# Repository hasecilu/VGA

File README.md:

# VGA adapter
This is a simple PCB board for interfacing a FPGA with SIL header to a VGA connector to add video functionalities to your projects.
Designed with [KiCad](https://kicad.org/download/)

[Download here](https://gitlab.com/hasecilu/VGA/-/archive/master/VGA-master.zip)

## Important!

For updates go to the [GitLab repo](https://gitlab.com/hasecilu/VGA)

## Pictures

First render

Second render

Third render

Fourth render

Please note that the VGA board showed in the next pictures are from an older version and that's the reason there is a cable for connecting ground.
The new version has ground pins on both sides to avoid use cables (generally ground pins are at the begin/end of one SIL header in the development boards).

Perspective view

Top view

## Using the PCB

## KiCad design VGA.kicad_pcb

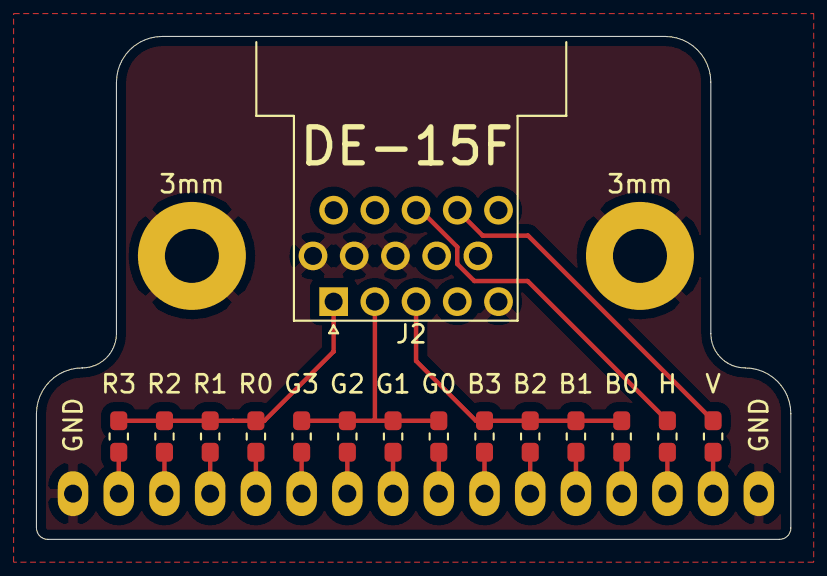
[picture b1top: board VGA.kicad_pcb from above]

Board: 2 copper layers, 41.9 x 27.9 mm, 18 parts (1 on the bottom side), 20 nets.

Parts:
3mm, 3mm#2: MountingHole_3mm_Pad
J1: Conn_01x16; PinHeader_1x16_P2.54mm_Vertical
J2: DB15_Female_HighDensity; DSUB-15-HD_Female_Horizontal_P2.29x2.54mm_EdgePinOffset9.40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
R1, R5, R9: 510; R_0603_1608Metric_Pad1.05x0.95mm_HandSolder
R2, R6, R10: 1k; R_0603_1608Metric_Pad1.05x0.95mm_HandSolder
R3, R7, R11: 2k; R_0603_1608Metric_Pad1.05x0.95mm_HandSolder
R4, R8, R12: 4k; R_0603_1608Metric_Pad1.05x0.95mm_HandSolder
R13, R14: 82; R_0603_1608Metric_Pad1.05x0.95mm_HandSolder

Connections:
/B: J2.3, R9.1, R10.1, R11.1, R12.1
/G: J2.2, R5.1, R6.1, R7.1, R8.1
/H: J2.13, R13.1
/R: J2.1, R1.1, R2.1, R3.1, R4.1
/V: J2.14, R14.1
GND: 3mm.1, 3mm#2.1, J1.1, J1.16, J2.5, J2.6, J2.7, J2.8, J2.10
unnamed: J1.2, R14.2
unnamed: J1.3, R13.2
unnamed: J1.4, R12.2
unnamed: J1.5, R11.2
unnamed: J1.6, R10.2
unnamed: J1.7, R9.2
unnamed: J1.8, R8.2
unnamed: J1.9, R7.2
unnamed: J1.10, R6.2
unnamed: J1.11, R5.2
unnamed: J1.12, R4.2
unnamed: J1.13, R3.2
unnamed: J1.14, R2.2
unnamed: J1.15, R1.2

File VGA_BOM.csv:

"Source:","/home/uli/Documents/KiCAD/Boards/VGA/VGA.sch"
"Date:","Fri 13 Dec 2019 15:05:54 CST"
"Tool:","Eeschema 5.1.5-52549c5~84~ubuntu18.04.1"
"Generator:","/usr/share/kicad/plugins/bom_csv_grouped_by_value.py"
"Component Count:","16"

"Individual Components:"

"Item","Qty","Reference(s)","Value","LibPart","Footprint","Datasheet"
"","","J1","Conn_01x16","Connector_Generic:Conn_01x16","Connector_PinHeader_2.54mm:PinHeader_1x16_P2.54mm_Vertical","~"
"","","J2","DB15_Female_HighDensity","Connector:DB15_Female_HighDensity","Connector_Dsub:DSUB-15-HD_Female_Horizontal_P2.29x2.54mm_EdgePinOffset9.40mm"," ~"
"","","R1","510","Device:R","Resistor_SMD:R_0603_1608Metric_Pad1.05x0.95mm_HandSolder","~"
"","","R2","1k","Device:R","Resistor_SMD:R_0603_1608Metric_Pad1.05x0.95mm_HandSolder","~"
"","","R3","2k","Device:R","Resistor_SMD:R_0603_1608Metric_Pad1.05x0.95mm_HandSolder","~"
"","","R4","4k","Device:R","Resistor_SMD:R_0603_1608Metric_Pad1.05x0.95mm_HandSolder","~"
"","","R5","510","Device:R","Resistor_SMD:R_0603_1608Metric_Pad1.05x0.95mm_HandSolder","~"
"","","R6","1k","Device:R","Resistor_SMD:R_0603_1608Metric_Pad1.05x0.95mm_HandSolder","~"
"","","R7","2k","Device:R","Resistor_SMD:R_0603_1608Metric_Pad1.05x0.95mm_HandSolder","~"
"","","R8","4k","Device:R","Resistor_SMD:R_0603_1608Metric_Pad1.05x0.95mm_HandSolder","~"
"","","R9","510","Device:R","Resistor_SMD:R_0603_1608Metric_Pad1.05x0.95mm_HandSolder","~"
"","","R10","1k","Device:R","Resistor_SMD:R_0603_1608Metric_Pad1.05x0.95mm_HandSolder","~"
"","","R11","2k","Device:R","Resistor_SMD:R_0603_1608Metric_Pad1.05x0.95mm_HandSolder","~"
"","","R12","4k","Device:R","Resistor_SMD:R_0603_1608Metric_Pad1.05x0.95mm_HandSolder","~"
"","","R13","82","Device:R","Resistor_SMD:R_0603_1608Metric_Pad1.05x0.95mm_HandSolder","~"
"","","R14","82","Device:R","Resistor_SMD:R_0603_1608Metric_Pad1.05x0.95mm_HandSolder","~"



"Collated Components:"

"Item","Qty","Reference(s)","Value","LibPart","Footprint","Datasheet"
"1","1","J1","Conn_01x16","Connector_Generic:Conn_01x16","Connector_PinHeader_2.54mm:PinHeader_1x16_P2.54mm_Vertical","~"
"2","1","J2","DB15_Female_HighDensity","Connector:DB15_Female_HighDensity","Connector_Dsub:DSUB-15-HD_Female_Horizontal_P2.29x2.54mm_EdgePinOffset9.40mm"," ~"
"3","3","R1, R5, R9","510","Device:R","Resistor_SMD:R_0603_1608Metric_Pad1.05x0.95mm_HandSolder","~"
"4","3","R2, R6, R10","1k","Device:R","Resistor_SMD:R_0603_1608Metric_Pad1.05x0.95mm_HandSolder","~"
"5","3","R3, R7, R11","2k","Device:R","Resistor_SMD:R_0603_1608Metric_Pad1.05x0.95mm_HandSolder","~"
"6","3","R4, R8, R12","4k","Device:R","Resistor_SMD:R_0603_1608Metric_Pad1.05x0.95mm_HandSolder","~"
"7","2","R13, R14","82","Device:R","Resistor_SMD:R_0603_1608Metric_Pad1.05x0.95mm_HandSolder","~"

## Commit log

2019-12-19 First public release
    This is the first version I release
2020-12-18 New renders
2020-12-18 Small changes
